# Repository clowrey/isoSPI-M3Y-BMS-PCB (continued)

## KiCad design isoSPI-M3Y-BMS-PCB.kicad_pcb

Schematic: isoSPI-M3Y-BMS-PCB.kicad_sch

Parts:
BT1, BT3, BT4, BT5, BT6, BT7, BT8, BT9: ~100V Brick
C1, C2, C55, C57: 10uF; C_0805_2012Metric; Voltage 50V; JLCPCB Part # C440198
C3, C4: 4.7uF 50V; C_1206_3216Metric; JLCPCB Part # C29823
C5, C94: 100nf; C_0603_1608Metric_Pad1.08x0.95mm_HandSolder; JLCPCB Part # C14663
C6, C24, C29: 10uF; C_0805_2012Metric; Voltage 50V X5R; JLCPCB Part # C440198
C7, C9, C49, C50, C51, C52, C62, C95, C132: 22uF; C_0805_2012Metric; Voltage 25V X5R; JLCPCB Part # C45783
C8: 10uF; C_0805_2012Metric_Pad1.18x1.45mm_HandSolder; Voltage 50V; JLCPCB Part # C440198
C10, C41, C42, C43: 100nf; C_0603_1608Metric; JLCPCB Part # C14663
C11, C38: 22uF; C_0805_2012Metric_Pad1.18x1.45mm_HandSolder; Voltage 25V; JLCPCB Part # C45783
C12, C13, C14, C15, C16, C21, C22, C23, C25, C28, C33, C44, C45, C54, C76, C79, C80, C81, C82, C85: 100nF; C_0603_1608Metric; JLCPCB Part # C14663
C17, C19, C20, C86: 1uF; C_0603_1608Metric; JLCPCB Part # v
C18: 1uF; C_0603_1608Metric; JLCPCB Part # C15849
C26, C40: 1uF; C_0603_1608Metric_Pad1.08x0.95mm_HandSolder; JLCPCB Part # C15849
C27, C32, C47, C61, C69, C72: 4.7u; C_0402_1005Metric; JLCPCB Part # C23733
C30, C31, C68: 100pF; C_0603_1608Metric; JLCPCB Part # C14858
C34, C112: 680uF; CP_Radial_D10.0mm_P5.00mm; Voltage 35V Polymer
C35, C36, C117, C118: 15pF; C_0402_1005Metric; JLCPCB Part # C1548
C37, C48, C87, C89: 4.7u; C_0402_1005Metric_small_pads; JLCPCB Part # C23733
C39, C56: 100nF; C_0603_1608Metric_Pad1.08x0.95mm_HandSolder; JLCPCB Part # C14663
C46, C58, C59, C60, C63, C64, C65, C66, C67, C70, C71, C73, C74, C75, C78, C120, C123, C124, C126, C127, C128, C129, C130, C131: 100n; C_0402_1005Metric; JLCPCB Part # C1525
C53: 4.7uF; C_0603_1608Metric; JLCPCB Part # C19666
D1, D7, D10, D25: SM15T36CA; D_SMC; JLCPCB Part # C1976312
D2, D3, D4, D8, D19, D38: Green; LED_0805_2012Metric; JLCPCB Part # C2297
D5, D23, D26, D29, D31, D32, D40: White; LED_0805_2012Metric; JLCPCB Part # C34499
D6, D9, D11, D14, D15, D21, D24, D30, D36, D39, D53: SS54; D_SMA; JLCPCB Part # C22452
D12, D13, D16, D17, D18, D20, D22, D27, D41, D42, D49, D50, D51: SMB6.8CA; D_SMB; JLCPCB Part # C78395
D28, D33, D34, D37: Red; LED_0805_2012Metric; JLCPCB Part # C84256
F1, F8: Pyro Fuse
F9, F11: 63A HV DC
FB1, FB7: 120Ω@100MHz; C_0603_1608Metric; JLCPCB Part # C14709
FB5: 600R@100MHz; L_0603_1608Metric_Pad1.05x0.95mm_HandSolder; JLCPCB Part # C1002
FL3: SDCW3225S-2-102TF; FILTER-SMD_4P-L3.2-W2.5-BL; JLCPCB Part # C192586
H1, H2, H3, H4, H5, H7, H12, H13: MountingHole_Pad; MountingHole_6.5mm
J1, J10: Screw_Terminal_01x04; PhoenixContact_MC_1,5_4-G-3.81_1x04_P3.81mm_Horizontal
J2, J13: Conn_02x10_Odd_Even; PinHeader_2x10_P2.54mm_Vertical
J3: 8P8C_LED_Shielded_x2; RJ45_Amphenol_RJHSE538X-02; JLCPCB Part # C3010546
J5: OEM Shunt Connector; CONN_ZE05H-8DP-2H_HIR
J6: 349128020; CONN_SD-34912-001_02_MOL; JLCPCB Part # C587318
J7: OEM HV Sense Connector; CONN_173864-1_TYC
J8: OEM Connector; S44BRAD1AK
J9, J16: Conn_01x03; PinHeader_1x03_P2.54mm_Vertical
J11: Screw_Terminal_01x03; PhoenixContact_MC_1,5_2-G-3.81_1x02_P3.81mm_Horizontal
J12: Screw_Terminal_01x08; PhoenixContact_MC_1,5_8-G-3.81_1x08_P3.81mm_Horizontal
J14: Screw_Terminal_01x04; PhoenixContact_GMSTBA_2,5_4-G-7,62_1x04_P7.62mm_Horizontal
J15, J17, J18: USB_C_Receptacle_USB2.0_16P; USB_C_Receptacle_HRO_TYPE-C-31-M-12
JP1, JP2, JP7, JP8: SolderJumper_3_Bridged12; SolderJumper-3_P1.3mm_Bridged12_RoundedPad1.0x1.5mm_NumberL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
JP3, JP4, JP5, JP6, JP13, JP14: SolderJumper_3_Open; SolderJumper-3_P1.3mm_Open_RoundedPad1.0x1.5mm_NumberLabels
JP9: SolderJumper_2_Bridged; SolderJumper-2_P1.3mm_Bridged_RoundedPad1.0x1.5mm
JP10, JP11, JP12: Jumper_2_Open; SolderJumper-2_P1.3mm_Open_RoundedPad1.0x1.5mm
K9, K14: Link Positive
K10, K16: FC Positive
K11, K17: FC Negative
K12, K15: Link Negative
K13, K18: Inverter
L1, L2, L4, L5: 6.8uh; L_Changjiang_FXL0630; JLCPCB Part # C167221
L3, L8: 22uh 5.5A; L_Changjiang_FXL1040; JLCPCB Part # C475917
L6, L7: 3.3u; L_pol_2016
Q1, Q2, Q3, Q5: CRSM034N06L2; AO_DFN-8-1EP_5.55x5.2mm_P1.27mm_EP4.12x4.6mm; JLCPCB Part # C467174
R1, R10: 150r; R_0603_1608Metric; JLCPCB Part # C22808
R2, R8: 2.2k; R_0603_1608Metric; JLCPCB Part # C4190
R3, R11, R27, R40, R41, R45, R47, R70, R74, R146: 24k; R_0603_1608Metric; JLCPCB Part # C23352
R4, R17, R25, R28, R62, R150: 100k; R_0603_1608Metric; JLCPCB Part # C25803
R5, R6, R26, R69, R90: 100R; R_0603_1608Metric; JLCPCB Part # C22775
R7, R9, R111, R112, R141: 510r; R_0603_1608Metric; JLCPCB Part # C23193
R12, R13, R14, R15, R20, R44, R53, R55, R82, R85, R174, R175: 5.1k; R_0603_1608Metric; JLCPCB Part # C23186
R16, R29, R48, R54, R56, R60, R66, R67, R68, R75, R77, R79, R83, R84, R140, R142, R143, R144, R148, R190: 10k; R_0603_1608Metric; JLCPCB Part # C25804
R18: 120r; R_1206_3216Metric; JLCPCB Part # C17909
R19, R33, R50, R58, R80, R171: 33r; R_0402_1005Metric; JLCPCB Part # C25105
R21, R24, R51, R52: 22R; R_0402_1005Metric; JLCPCB Part # C25092
R22, R31, R81: 10k; R_0603_1608Metric_Pad0.98x0.95mm_HandSolder; JLCPCB Part # C25804
R23, R36, R37, R38, R39, R42: 1.8k; R_0603_1608Metric; JLCPCB Part # C4177
R30: 100r; R_0603_1608Metric; JLCPCB Part # C22775
R32, R178: 25296nΩ
R34, R35, R43, R46, R49, R57, R59, R63, R64, R167, R168, R170: 1k; R_0402_1005Metric; JLCPCB Part # C11702
R61: 3k; R_0603_1608Metric; JLCPCB Part # C4211
R65: 2.7k; R_0603_1608Metric; JLCPCB Part # C13167
R94, R97: 1k; R_0603_1608Metric; JLCPCB Part # C21190
R98, R99, R100, R101, R102, R103, R104, R105, R106, R107, R108, R109, R110, R114, R115, R116, R126, R127, R130, R131, R134, R135, R153, R155, R193, R194, R195, R196, R214, R215, R216, R217, R218, R219, R220, R221, R222, R223, R224, R225, R226, R227: 1M; R_1206_3216Metric; JLCPCB Part # C17927
R149, R228, R229: 220r; R_0603_1608Metric; JLCPCB Part # C22962
R176: 27R 50W
SW1, SW2, SW3, SW4: TS-1187A-B-A-B; SW_Push_1P1T_XKB_TS-1187A; JLCPCB Part # C318884
TH1, TH2, TH3, TH4, TH5, TH6: B59451C1130B070; RV_Disc_D15.5mm_W7.5mm_P5.0mm; JLCPCB Part # C2762811
TP1, TP2, TP3, TP4, TP5, TP6, TP7, TP8, TP9, TP15, TP16, TP17, TP18, TP19: TestPoint_2Pole; TestPoint_2Pads_Pitch2.54mm_Pad1.5_Drill1.0mm
TP10, TP11, TP12, TP13, TP14: TP; TestPoint_THTPad_D1.5mm_Drill1.0mm
TR10: HM2113ZNLT; JLCPCB Part # C5730533
U1, U15, U23, U25, U26: SN74LV1T08DBVR; SOT-23-5; JLCPCB Part # C2682144
U2, U4, U30: ISO1540; SOIC-8_3.9x4.9mm_P1.27mm; JLCPCB Part # C179739
U3: INA228; VSSOP-10_3x3mm_P0.5mm; JLCPCB Part # C5214669
U6, U22, U24: F0505S-1WR3; Converter_DCDC_TRACO_TEA1-xxxxHI_THT; JLCPCB Part # C7465182
U8, U9, U10, U20: LTV-217-B-G; SSOP-4_4.4x2.6mm_P1.27mm; JLCPCB Part # C115450
U11, U27: RP2354B; RP2350-QFN-80-1EP_10x10_P0.4mm_EP3.4x3.4mm_ThermalVias; JLCPCB Part # C39843328
U12: ADS1115; TSSOP-10_3x3mm_P0.5mm; LCSC Part # C37593
U13: ISO1050DUB; SOP-8_6.62x9.15mm_P2.54mm; LCSC Part # C16428
U16: BatMan; LQFP-64_10x10mm_P0.5mm; JLCPCB Part # DNP
U17: TPS5430DDAR; TI_SO-PowerPAD-8_ThermalVias; LCSC Part C9864
U21: AMS1117-3.3; SOT-223-3_TabPin2; JLCPCB Part # C6186
U28: AM26LV32EIDR; SOIC-16_3.9x9.9mm_P1.27mm; JLCPCB Part # C527448
U29: B0505S-3WR2; Converter_DCDC_TRACO_TRA3-xxxx_THT; LCSC Part # C7500927
U32: SP3485EN-L/TR; SOIC-8_3.9x4.9mm_P1.27mm; JLCPCB Part # C8963
Y1, Y2: ABM8-272-T3; Crystal_SMD_3225-4Pin_3.2x2.5mm; JLCPCB Part # C20625731

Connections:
3.3V Sense: R66.2, R67.1, U27.49 (GPIO40_ADC0)
5V Sense: R140.1, R146.2, U27.52 (GPIO41_ADC1)
+1V1: C48.1, C71.1, C120.1, C123.1, L7.1, U27.10 (DVDD), U27.32 (DVDD), U27.51 (DVDD), U27.65 (VREG_FB)
+1V1_2: C46.1, C58.1, C70.1, C87.1, L6.1, U11.10 (DVDD), U11.32 (DVDD), U11.51 (DVDD), U11.65 (VREG_FB)
+3.3V: C13.1, C14.1, C37.1, C53.2, C59.1, C60.1, C63.1, C64.1, C65.1, C66.1, C67.1, C73.1, C74.1, C75.1, C78.1, C89.1, C124.1, C126.1, C127.1, C128.1, C129.1, C130.1, C131.1, J2.1, J2.3, J2.5, J2.7, J2.9, J13.1, J13.3, J13.5, J13.7, J13.9, R12.1, R13.1, R19.2, R33.2, R50.2, R58.2, R59.1, R65.2, R66.1, R75.1, R82.1, R85.1, R94.1, TP7.2, U2.1 (VCC1), U4.1 (VCC1), U8.4, U9.4, U11.5 (IOVDD), U11.15 (IOVDD), U11.24 (IOVDD), U11.29 (IOVDD), U11.41 (IOVDD), U11.50 (IOVDD), U11.60 (IOVDD), U11.64 (VREG_VIN), U11.68 (USB_OTP_VDD), U11.69 (QSPI_IOVDD), U11.76 (IOVDD), U13.1 (VCC1), U21.2 (VO), U27.5 (IOVDD), U27.15 (IOVDD), U27.24 (IOVDD), U27.29 (IOVDD), U27.41 (IOVDD), U27.50 (IOVDD), U27.60 (IOVDD), U27.64 (VREG_VIN), U27.68 (USB_OTP_VDD), U27.69 (QSPI_IOVDD), U27.76 (IOVDD), U30.1 (VCC1)
+3V3: C21.1, C22.2, C25.1, U1.5 (VCC), U28.4 (G), U28.16 (VDD), U32.8 (VCC)
+5V: C9.2, C11.2, C23.1, C49.2, C50.2, C52.2, C79.2, C80.2, C81.2, C82.2, C112.1, C132.2, FB1.2, FB7.2, L1.2, L2.2, L4.2, L5.2, L8.1, R60.1, R146.1, R190.1, TP8.2, U15.5 (VCC), U16.5 (5V), U16.41 (5V), U16.47 (5V), U21.3 (VI), U23.5 (VCC), U25.5 (VCC), U26.5 (VCC)
/CAN 5V: C6.2, C16.2, R23.2, R37.2, R77.1, R112.1, U13.8 (VCC2), U24.7 (+Vout)
/CAN H: C30.2, D16.2 (A2), FL3.2, JP1.3 (B), JP2.1 (A), JP3.3 (B), JP4.3 (B), JP5.3 (B), JP6.3 (B), JP13.3 (B), JP14.3 (B), R18.2, TP2.2
/CAN L: C31.1, D17.1 (A1), FL3.3, JP1.1 (A), JP2.3 (B), JP3.1 (A), JP4.1 (A), JP5.1 (A), JP6.1 (A), JP13.1 (A), JP14.1 (A), R18.1, TP2.1
/Contactor_Input: D15.2 (A), D20.2 (A2), D36.2 (A), J1.2
/FC Pos: K10.13, K16.13, K18.1, R176.2, TH1.2, TH2.2, TH3.2
/FC-Neg-Jumper: C44.2, D19.1 (K), D25.2 (A2), D39.2 (A), JP10.1 (A), JP11.1 (A), JP12.1 (A), Q3.5 (D)
/GPIO0: R57.2, U27.77 (GPIO0)
/GPIO3: J2.2, U27.80 (GPIO3)
/GPIO4: J2.4, U27.1 (GPIO4)
/GPIO5: J2.6, U27.2 (GPIO5)
/GPIO6: J2.8, U27.3 (GPIO6)
/GPIO7: J2.10, U27.4 (GPIO7)
/GPIO8: J2.12, U27.6 (GPIO8)
/GPIO9: J2.14, U27.7 (GPIO9)
/GPIO10: J2.16, U27.8 (GPIO10)
/GPIO11: J2.18, U27.9 (GPIO11)
/GPIO12: J2.20, U27.11 (GPIO12)
/GPIO25: R48.1, U27.26 (GPIO25)
/GPIO44_ADC4: U27.55 (GPIO44_ADC4)
/GPIO45_ADC5: U27.56 (GPIO45_ADC5)
/GPIO46_ADC6: U27.57 (GPIO46_ADC6)
/GPIO47_ADC7: U27.58 (GPIO47_ADC7)
/Grn: J3.6, JP14.2 (C)
/HV Sense 5V: C18.2, C39.2, C56.2, FB5.2, R20.1, R44.1, R54.1, R81.2, R228.1, U2.8 (VCC2), U12.8 (VDD)
/Logic_Input: D12.2 (A2), D14.2 (A), J1.4
/MCU2_GPIO0: R59.2, U11.77 (GPIO0)
/MCU2_GPIO1: R63.2, U11.78 (GPIO1)
/MCU2_GPIO2: R64.2, U11.79 (GPIO2)
/MCU2_GPIO3: U11.80 (GPIO3)
/MCU2_GPIO4: J13.2, U11.1 (GPIO4)
/MCU2_GPIO5: J13.4, U11.2 (GPIO5)
/MCU2_GPIO6: J13.6, U11.3 (GPIO6)
/MCU2_GPIO7: J13.8, U11.4 (GPIO7)
/MCU2_GPIO8: J13.10, U11.6 (GPIO8)
/MCU2_GPIO9: J13.12, U11.7 (GPIO9)
/MCU2_GPIO10: J13.14, U11.8 (GPIO10)
/MCU2_GPIO11: J13.16, U11.9 (GPIO11)
/MCU2_GPIO12: J13.18, U11.11 (GPIO12)
/MCU2_GPIO13: J13.20, U11.12 (GPIO13)
/MCU2_GPIO15: U11.14 (GPIO15)
/MCU2_GPIO16: U11.16 (GPIO16)
/MCU2_GPIO17: U11.17 (GPIO17)
/MCU2_GPIO18: U11.18 (GPIO18)
/MCU2_GPIO19: U11.19 (GPIO19)
/MCU2_GPIO20: U11.20 (GPIO20)
/MCU2_GPIO21: U11.21 (GPIO21)
/MCU2_GPIO22: U11.22 (GPIO22)
/MCU2_GPIO23: U11.23 (GPIO23)
/MCU2_GPIO24: U11.25 (GPIO24)
/MCU2_GPIO25: R56.1, U11.26 (GPIO25)
/MCU2_GPIO26: U11.27 (GPIO26)
/MCU2_GPIO27: U11.28 (GPIO27)
/MCU2_GPIO33: U11.42 (GPIO33)
/MCU2_GPIO34: U11.43 (GPIO34)
/MCU2_GPIO35: U11.44 (GPIO35)
/MCU2_GPIO36: U11.45 (GPIO36)
/MCU2_GPIO37: U11.46 (GPIO37)
/MCU2_GPIO38: R34.2, U11.47 (GPIO38)
/MCU2_GPIO39: R35.2, U11.48 (GPIO39)
/PH: C54.1, D24.1 (K), L8.2, U17.8 (PH)
/QSPI2_SCLK: U11.71 (QSPI_SCLK)
/QSPI2_SD0: U11.72 (QSPI_SD0)
/QSPI2_SD1: U11.74 (QSPI_SD1)
/QSPI2_SD2: U11.73 (QSPI_SD2)
/QSPI2_SD3: U11.70 (QSPI_SD3)
/QSPI2_SS: R49.1, U11.75 (QSPI_SS)
/QSPI_SCLK: U27.71 (QSPI_SCLK)
/QSPI_SD0: U27.72 (QSPI_SD0)
/QSPI_SD1: U27.74 (QSPI_SD1)
/QSPI_SD2: U27.73 (QSPI_SD2)
/QSPI_SD3: U27.70 (QSPI_SD3)
/QSPI_SS: R170.1, U27.75 (QSPI_SS)
/RUN: R167.2, SW4.2
/RUN_2: R43.1, U11.35 (RUN)
/SWCLK: J16.1, U27.33 (SWCLK)
/SWCLK_2: J9.1, U11.33 (SWCLK)
/SWD: J16.3, U27.34 (SWD)
/SWD_2: J9.3, U11.34 (SWD)
/Serial API 5V: C12.2, C24.2, D21.2 (A), R97.1, R141.1, R142.1, U29.6 (+Vout), U30.8 (VCC2)
/Serial API RX: D42.1 (A1), J15.A7 (D-), J15.B7 (D-), R143.1, TP19.1, U30.6 (SCL2)
/Serial API TX: D41.2 (A2), J15.A6 (D+), J15.B6 (D+), R97.2, TP19.2, U30.7 (SDA2)
/USB2_D+: J17.A6 (D+), J17.B6 (D+), R51.1
/USB2_D-: J17.A7 (D-), J17.B7 (D-), R52.1
/USB_D+: J18.A6 (D+), J18.B6 (D+), R21.1
/USB_D-: J18.A7 (D-), J18.B7 (D-), R24.1
/VREG2_AVDD: C32.1, R33.1, U11.61 (VREG_AVDD)
/VREG2_LX: L6.2, U11.63 (VREG_LX)
/VREG_AVDD: C61.1, R19.1, U27.61 (VREG_AVDD)
/VREG_LX: L7.2, U27.63 (VREG_LX)
/V_cont1: C2.2, D15.1 (K), D36.1 (K), L3.2
/Wht-Grn: J3.3, JP13.2 (C)
/XIN: C117.1, U27.30 (XIN), Y2.1
/XIN_2: C35.1, U11.30 (XIN), Y1.1
/XOUT: R168.1, U27.31 (XOUT)
/XOUT_2: R46.1, U11.31 (XOUT)
/iso+: C68.2, JP7.2 (C), R90.1, TP18.1, TR10.1 (TD-)
/iso-: C68.1, JP8.2 (C), R90.2, TP18.2, TR10.3 (TD+)
BatSPI_EN: U16.42 (EN), U27.46 (GPIO37)
BatSPI_SCK: U16.56 (SPI_SCK), U27.43 (GPIO34)
Batman IsoSPI+: JP8.3 (B), U16.62 (A-BMB)
Batman IsoSPI-: JP7.3 (B), U16.61 (A-BMB)
Batt Negative: J7.10, J14.4, R225.2
Batt Positive: J7.1, J14.1, R224.2
C FC-Neg (GND): J8.37, J12.2, JP10.2 (B), JP11.2 (B), JP12.2 (B)
C FC-Pos (GND): C33.2, D1.2 (A2), D4.1 (K), D11.2 (A), J8.36, J12.4, Q2.5 (D)
C Neg (GND): C15.2, D3.1 (K), D6.2 (A), D7.2 (A2), J8.42, J12.6, Q1.5 (D)
C Pos (GND): C45.2, D8.1 (K), D9.2 (A), D10.2 (A2), J8.41, J12.8, Q5.5 (D)
CAN Rx: R83.1, TP6.1, U13.2 (RXD), U27.19 (GPIO19)
CAN Tx: R84.1, TP6.2, U13.3 (TXD), U27.20 (GPIO20)
C_En: U11.13 (GPIO14), U15.2, U23.2, U25.2, U26.2
Drive Unit Pos: F9.1, K9.13, K10.14, K14.13, K16.14, TH4.1, TH5.1, TH6.1
Emergency Stop: R22.2, U8.3
Extra Input: R31.2, U9.3
Extra Output 1: R39.2, U27.12 (GPIO13)
Extra Output 2: R38.2, U27.13 (GPIO14)
FC Negative: J7.7, J14.3, R227.2
FC Positive: J7.4, J14.2, R226.2
FC-Neg: U26.1, U27.14 (GPIO15)
FC-Pos: U25.1, U27.18 (GPIO18)
GND: C1.1, C2.1, C7.1, C9.1, C11.1, C13.2, C14.2, C15.1, C21.2, C22.1, C23.2, C25.2, C27.2, C32.2, C33.1, C34.2, C35.2, C36.2, C37.2, C38.1, C44.1, C45.1, C46.2, C47.2, C48.2, C49.1, C50.1, C51.1, C52.1, C53.1, C55.1, C57.1, C58.2, C59.2, C60.2, C61.2, C62.1, C63.2, C64.2, C65.2, C66.2, C67.2, C69.2, C70.2, C71.2, C72.2, C73.2, C74.2, C75.2, C78.2, C79.1, C80.1, C81.1, C82.1, C85.1, C87.2, C89.2, C112.2, C117.2, C118.2, C120.2, C123.2, C124.2, C126.2, C127.2, C128.2, C129.2, C130.2, C131.2, C132.1, D1.1 (A1), D2.1 (K), D5.1 (K), D7.1 (A1), D10.1 (A1), D22.1 (A1), D23.1 (K), D24.2 (A), D25.1 (A1), D26.1 (K), D28.1 (K), D33.1 (K), D34.1 (K), D37.1 (K), D49.1 (A1), D51.1 (A1), J1.1, J1.3, J2.11, J2.13, J2.15, J2.17, J2.19, J9.2, J13.11, J13.13, J13.15, J13.17, J13.19, J16.2, J17.A1 (GND), J17.A12 (GND), J17.B1 (GND), J17.B12 (GND), J17.S1 (SHIELD), J18.A1 (GND), J18.A12 (GND), J18.B1 (GND), J18.B12 (GND), J18.S1 (SHIELD), Q1.1 (S), Q1.2 (S), Q1.3 (S), Q2.1 (S), Q2.2 (S), Q2.3 (S), Q3.1 (S), Q3.2 (S), Q3.3 (S), Q5.1 (S), Q5.2 (S), Q5.3 (S), R4.1, R17.1, R22.1, R25.1, R29.2, R31.1, R53.1, R55.1, R57.1, R62.1, R67.2, R99.1, R140.2, R148.2, R149.2, R174.1, R175.1, SW1.1, SW2.1, SW3.1, SW4.1, TP7.1, TP8.1, TP15.1, TP16.1, U1.3 (GND), U2.4 (GND1), U4.4 (GND1), U6.2 (-Vin), U10.2, U11.62 (VREG_PGND), U11.81 (GND), U13.4 (GND1), U15.3 (GND), U16.1 (GND), U16.3 (GND), U16.6 (GND), U16.7 (GND), U16.8 (GND), U16.9 (GND), U16.10 (GND), U16.11 (GND), U16.12 (GND), U16.13 (GND), U16.14 (GND), U16.15 (GND), U16.16 (GND), U16.17 (GND), U16.18 (GND), U16.19 (GND), U16.20 (GND), U16.21 (GND), U16.22 (GND), U16.23 (GND), U16.24 (GND), U16.25 (GND), U16.26 (GND), U16.27 (GND), U16.28 (GND), U16.29 (GND), U16.30 (GND), U16.31 (GND), U16.33 (GND), U16.34 (GND), U16.35 (GND), U16.36 (GND), U16.37 (GND), U16.38 (GND), U16.39 (GND), U16.40 (GND), U16.43 (GND), U16.45 (GND), U16.46 (GND), U16.49 (GND), U16.51 (GND), U16.60 (GND), U17.6 (GND), U17.9 (PowerPAD), U20.2, U21.1 (GND), U22.2 (-Vin), U23.3 (GND), U24.2 (-Vin), U25.3 (GND), U26.3 (GND), U27.62 (VREG_PGND), U27.81 (GND), U28.8 (GND), U28.12 (~G), U29.2 (-Vin), U30.4 (GND1), U32.2 (~RE), U32.5 (GND), Y1.2, Y1.4, Y2.2, Y2.4
GND CAN: C6.1, C16.1, C30.1, C31.2, D16.1 (A1), D17.2 (A2), D29.1 (K), J3.19, J3.SH, R112.2, U13.5 (GND2), U24.5 (-Vout)
GND Shunt NTC -: C3.1, C4.2, C28.1, C29.1, C76.1, C94.1, D31.1 (K), J5.1, J5.3, J10.2, R7.1, R9.2, R111.2, U3.1 (A1), U3.2 (A0), U3.7 (GND), U4.5 (GND2), U22.5 (-Vout)
GND_RS: C12.1, C24.1, D38.1 (K), D40.1 (K), D41.1 (A1), D42.2 (A2), J15.A1 (GND), J15.A12 (GND), J15.B1 (GND), J15.B12 (GND), J15.S1 (SHIELD), R141.2, U29.4 (-Vout), U30.5 (GND2)
GND_VSens: C8.1, C18.1, C39.1, C56.1, C95.1, D32.1 (K), R229.2, TP12.1, U2.5 (GND2), U6.5 (-Vout), U12.1 (ADDR), U12.3 (GND)
HMI Serial RX: R35.1, R94.2, TP5.2, U27.48 (GPIO39), U30.3 (SCL1)
HMI Serial TX: R34.1, R144.1, TP5.1, U27.47 (GPIO38), U30.2 (SDA1)
I2C SCL Shunt: R12.2, TP3.2, U4.3 (SCL1), U27.23 (GPIO23)
I2C SCL Vsense: R82.2, TP4.2, U2.3 (SCL1), U27.21 (GPIO21)
I2C SDA Shunt: R13.2, TP3.1, U4.2 (SDA1), U27.25 (GPIO24)
I2C SDA Vsense: R85.2, TP4.1, U2.2 (SDA1), U27.22 (GPIO22)
IsoSPI RX AND: U1.4, U11.38 (GPIO30), U27.38 (GPIO30)
IsoSPI RX Debug: TP16.2, U11.39 (GPIO31), U27.39 (GPIO31)
IsoSPI RX H: TP17.1, U1.2, U11.36 (GPIO28), U27.36 (GPIO28), U28.5 (2Y)
IsoSPI RX L: TP17.2, U1.1, U11.37 (GPIO29), U27.37 (GPIO29), U28.3 (1Y)
IsoSPI TX Data: TP1.2, U27.28 (GPIO27), U32.4 (DI)
IsoSPI TX En: TP1.1, U27.27 (GPIO26), U32.3 (DE)
IsoSPI+: J6.1, J11.1, TR10.4 (TX+)
IsoSPI-: J6.2, J11.2, TR10.6 (TX-)
Link Negative: J7.22
Link Positive: J7.13
MAIN-SUP TX/RX: R64.1, TP9.2, U27.78 (GPIO1)
Neg: U23.1, U27.16 (GPIO16)
unnamed: BT1.1 (+), BT5.2 (-)
unnamed: BT1.2 (-), R32.2
unnamed: BT3.1 (+), F8.1
unnamed: BT3.2 (-), BT4.1 (+)
unnamed: BT4.2 (-), BT9.2 (-), K12.14, K15.14
unnamed: BT5.1 (+), BT6.1 (+), K9.14, K14.14, R176.1
unnamed: BT6.2 (-), BT7.1 (+)
unnamed: BT7.2 (-), R178.1
unnamed: BT8.1 (+), F1.1
unnamed: BT8.2 (-), BT9.1 (+)
unnamed: C3.2, R8.2, R10.1
unnamed: C4.1, R1.1, R2.2
unnamed: C10.1, C41.2, C42.1, C43.2, C95.2, R40.2, R41.1, R45.2, R47.1, R228.2, R229.1
unnamed: C26.1, J3.14, J3.23, U9.2
unnamed: C26.2, R36.1, U9.1
unnamed: C27.1, R50.1, R80.2
unnamed: C36.1, R46.2, Y1.3
unnamed: C40.1, J3.20, J3.21, U8.2
unnamed: C40.2, R23.1, U8.1
unnamed: C69.1, R58.1, R171.2
unnamed: C118.1, R168.2, Y2.3
unnamed: D2.2 (A), R83.2
unnamed: D3.2 (A), R11.2
unnamed: D4.2 (A), R27.2
unnamed: D5.2 (A), R74.2
unnamed: D8.2 (A), R3.2
unnamed: D12.1 (A1), D13.2 (A2)
unnamed: D13.1 (A1), D22.2 (A2)
unnamed: D18.1 (A1), D50.2 (A2)
unnamed: D19.2 (A), R70.2
unnamed: D20.1 (A1), D27.2 (A2)
unnamed: D21.1 (K), J15.A4 (VBUS), J15.A9 (VBUS), J15.B4 (VBUS), J15.B9 (VBUS)
unnamed: D23.2 (A), R190.2
unnamed: D26.2 (A), R75.2
unnamed: D27.1 (A1), D49.2 (A2)
unnamed: D28.2 (A), R84.2
unnamed: D29.2 (A), R77.2
unnamed: D30.2 (A), J17.A4 (VBUS), J17.A9 (VBUS), J17.B4 (VBUS), J17.B9 (VBUS)
unnamed: D30.1 (K), FB1.1
unnamed: D31.2 (A), R79.2
unnamed: D32.2 (A), R81.1
unnamed: D33.2 (A), R48.2
unnamed: D34.2 (A), R56.2
unnamed: D37.2 (A), R144.2
unnamed: D38.2 (A), R143.2
unnamed: D40.2 (A), R142.2
unnamed: D50.1 (A1), D51.2 (A2)
unnamed: D53.2 (A), J18.A4 (VBUS), J18.A9 (VBUS), J18.B4 (VBUS), J18.B9 (VBUS)
unnamed: D53.1 (K), FB7.1
unnamed: F1.2, R178.4
unnamed: F8.2, R32.1
unnamed: F9.2, K13.1
unnamed: F11.1, K11.14, K12.13, K13.2, K15.13, K17.14
unnamed: F11.2, K11.13, K17.13, K18.2
unnamed: J3.13, R36.2, R42.2
unnamed: J3.15, U20.4
unnamed: J3.16, U10.3
unnamed: J3.17, U10.4
unnamed: J3.18, U20.3
unnamed: J3.22, R37.1
unnamed: J3.24, R42.1
unnamed: J17.A5 (CC1), R53.2
unnamed: J17.B5 (CC2), R55.2
unnamed: J18.A5 (CC1), R174.2
unnamed: J18.B5 (CC2), R175.2
unnamed: J3.5, JP1.2 (C)
unnamed: J3.4, JP2.2 (C)
unnamed: J3.8, JP3.2 (C)
unnamed: J3.7, JP4.2 (C)
unnamed: J3.2, JP5.2 (C)
unnamed: J3.1, JP6.2 (C)
unnamed: C20.1, C86.1, JP7.1 (A), U32.6 (A)
unnamed: C17.1, C19.1, JP8.1 (A), U32.7 (B)
unnamed: JP9.1 (A), TR10.2 (C_TD)
unnamed: C85.2, JP9.2 (B)
unnamed: Q1.4 (G), R5.2
unnamed: Q2.4 (G), R6.2
unnamed: Q3.4 (G), R69.2
unnamed: Q5.4 (G), R26.2
unnamed: R4.2, R5.1, U23.4
unnamed: R6.1, R17.2, U25.4
unnamed: R25.2, R26.1, U15.4
unnamed: R30.1, U16.64 (B-BMB)
unnamed: R30.2, U16.63 (B-BMB)
unnamed: R38.1, U20.1
unnamed: R39.1, U10.1
unnamed: R43.2, SW2.2
unnamed: R49.2, SW1.2
unnamed: R62.2, R69.1, U26.4
unnamed: R98.1, R99.2
unnamed: R100.2, R104.1
unnamed: R101.2, R105.1
unnamed: R102.2, R106.1
unnamed: R103.2, R107.1
unnamed: R104.2, R108.1
unnamed: R105.2, R109.1
unnamed: R106.2, R110.1
unnamed: R107.2, R114.1
unnamed: R108.2, R115.1
unnamed: R109.2, R116.1
unnamed: R110.2, R126.1
unnamed: R114.2, R127.1
unnamed: R115.2, R130.1
unnamed: R116.2, R131.1
unnamed: R126.2, R134.1
unnamed: R127.2, R135.1
unnamed: R130.2, R153.1
unnamed: R131.2, R155.1
unnamed: R134.2, R193.1
unnamed: R135.2, R194.1
unnamed: R61.2, R149.1
unnamed: R153.2, R195.1
unnamed: R155.2, R196.1
unnamed: R170.2, SW3.2
unnamed: R193.2, R214.1
unnamed: R194.2, R215.1
unnamed: R195.2, R216.1
unnamed: R196.2, R217.1
unnamed: R214.2, R218.1
unnamed: R215.2, R219.1
unnamed: R216.2, R220.1
unnamed: R217.2, R221.1
unnamed: R218.2, R222.1
unnamed: R219.2, R223.1
unnamed: R220.2, R224.1
unnamed: R221.2, R225.1
unnamed: R222.2, R226.1
unnamed: R223.2, R227.1
unnamed: TH1.1, TH2.1, TH3.1, TH4.2, TH5.2, TH6.2
unnamed: R98.2, TR10.5 (C_TX)
unnamed: R15.2, U3.5 (SCL), U4.6 (SCL2)
unnamed: R14.2, U3.4 (SDA), U4.7 (SDA2)
unnamed: C5.2, R2.1, U3.10 (Vin+)
unnamed: C5.1, R8.1, U3.9 (Vin-)
unnamed: R68.2, U3.3 (~Alert)
unnamed: C38.2, L2.1, U6.1 (+Vin)
unnamed: C8.2, FB5.1, U6.7 (+Vout)
unnamed: C47.1, R80.1, U11.59 (ADC_AVDD)
unnamed: R52.2, U11.66 (USB_DM)
unnamed: R51.2, U11.67 (USB_DP)
unnamed: C10.2, R40.1, R100.1, TP14.1, U12.4 (AIN0)
unnamed: C41.1, R41.2, R101.1, TP13.1, U12.5 (AIN1)
unnamed: C42.2, R45.1, R102.1, TP11.1, U12.6 (AIN2)
unnamed: C43.1, R47.2, R103.1, TP10.1, U12.7 (AIN3)
unnamed: R54.2, U12.2 (ALERT/RDY)
unnamed: R44.2, U2.6 (SCL2), U12.10 (SCL)
unnamed: R20.2, U2.7 (SDA2), U12.9 (SDA)
unnamed: FL3.1, U13.7 (CANH)
unnamed: FL3.4, U13.6 (CANL)
unnamed: C54.2, U17.1 (BOOT)
unnamed: R60.2, R61.1, U17.4 (VSENSE)
unnamed: C7.2, L1.1, U22.1 (+Vin)
unnamed: C62.2, L5.1, U24.1 (+Vin)
unnamed: C72.1, R171.1, U27.59 (ADC_AVDD)
unnamed: R167.1, U27.35 (RUN)
unnamed: R24.2, U27.66 (USB_DM)
unnamed: R21.2, U27.67 (USB_DP)
unnamed: C86.2, U28.2 (1A)
unnamed: C17.2, U28.1 (1B)
unnamed: C19.2, U28.6 (2A)
unnamed: C20.2, U28.7 (2B)
unnamed: C51.2, L4.1, U29.1 (+Vin)
Pos: U15.1, U27.17 (GPIO17)
SUP-MAIN TX/RX: R63.1, TP9.1, U27.79 (GPIO2)
Shunt Midpoint: J5.8
Shunt NTC +: C94.2, J5.7, J10.1, R16.1, U3.8 (Vbus)
Shunt Passive +: J5.6
Shunt Sense +: J5.5, J10.3, R1.2, R7.2
Shunt Sense -: J5.4, J10.4, R9.1, R10.2
Shunt_5V: C28.2, C29.2, C76.2, R14.1, R15.1, R16.2, R68.1, R79.1, R111.1, U3.6 (VS), U4.8 (VCC2), U22.7 (+Vout)
Snooper Debug: TP15.2, U11.40 (GPIO32), U27.40 (GPIO32)
VContactor Sense: R28.1, R29.1, U27.54 (GPIO43_ADC3)
V_{Contactor}: C1.2, C34.1, D6.1 (K), D9.1 (K), D11.1 (K), D18.2 (A2), D39.1 (K), J8.33, J8.34, J8.35, J8.43, J12.1, J12.3, J12.5, J12.7, L3.1, R3.1, R11.1, R27.1, R28.2, R70.1
V_{in}: C55.2, C57.2, D14.1 (K), R74.1, R150.2, U17.7 (VIN)
Vin Logic Sense: R148.1, R150.1, U27.53 (GPIO42_ADC2)

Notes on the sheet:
all JLC basic components
3.3V 1A LDO Supply
GPIO3 - GPIO12 on NC header
FC Negative Contactor
Would be cool if it alternates with main
PTC 440V 56Ω
BMB side xfmr center tap has no connection reference to ground to prevent ESD
unused inputs left floating - internal bias
3A max output - 3.3V draws from this rail
Galvanically Isolated Area
100k input impedance 0.14mA typical ADC usage
Terminate unused port per LTC6813 datasheet (100R recommended)
MCU Identification
In tesla packs the shunt is at the mid point of the pack!
Supervisor MCU
5V powers exteral ESP32 LCD also
FC Positive Contactor
Cells Positive Contactor
close to MCU
Extra GPIO
API TTL RS232 Interface
Redundant connectors
isoSPI Transceiver
Shunt Current Sense
Cells Positive Always Live
10V-16V input
Data must be after En
Positives
all JLC basic components except: inductor, 680uf cap
1A max output
Inverter connected to FC port
5V 3A DC-DC Supply
5V 600mA max external ESP32 interface
BatMan Interface
Inverter CAN Interface
Cells Negative Contactor
I2C ADDR: 0x48
requires connection to always live terminal
Contactor AND gate enable output
Main MCU

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
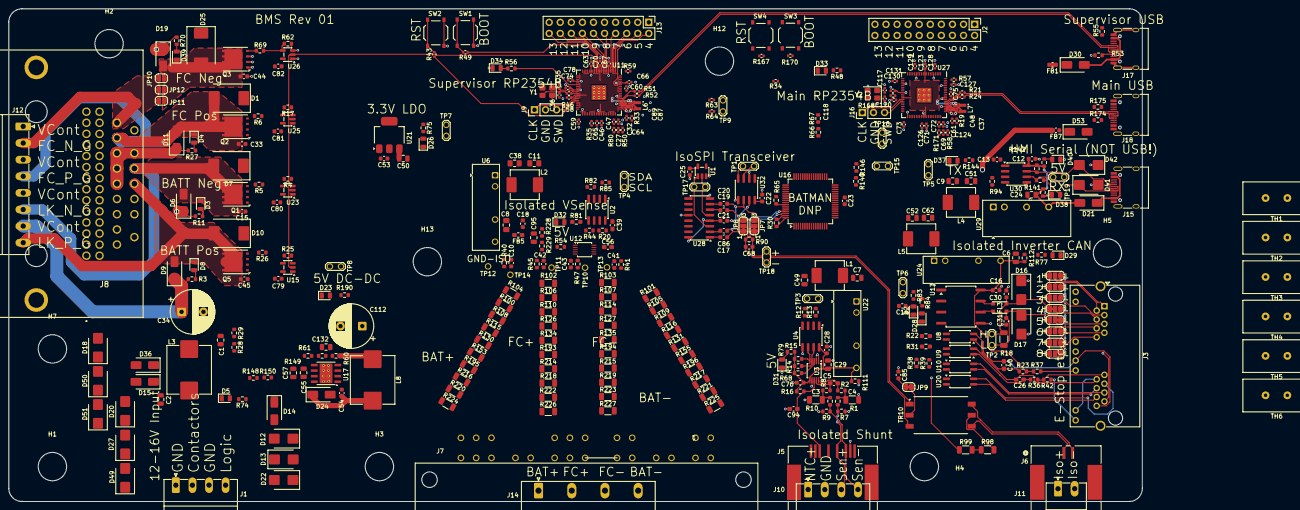
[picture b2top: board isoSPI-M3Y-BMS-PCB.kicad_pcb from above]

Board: 4 copper layers, 260.0 x 113.0 mm, 402 parts (0 on the bottom side), 275 nets.

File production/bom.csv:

Designator,Footprint,Quantity,Value,LCSC Part #
"C1, C2, C24, C29, C55, C57, C6, C8",0805,8,10uF,C440198
"C10, C12, C13, C14, C15, C16, C21, C22, C23, C25, C28, C33, C39, C41, C42, C43, C44, C45, C5, C54, C56, C76, C77, C79, C80, C81, C82, C83, C84, C85, C88, C94",0603,32,100nf,C14663
"C11, C132, C38, C49, C50, C51, C52, C62, C7, C9, C95",0805,11,22uF,C45783
"C112, C34, C69",CP_Radial_D10.0mm_P5.00mm,3,680uF,C46550429
"C117, C118, C35, C36",0402,4,15pF,C1548
"C120, C123, C124, C126, C127, C128, C129, C130, C131, C46, C58, C59, C60, C63, C64, C65, C66, C67, C70, C71, C73, C74, C75, C78",0402,24,100n,C1525
"C17, C19, C20, C86",0603,4,1uF,v
"C18, C26, C27, C40, C90",0603,5,1uF,C15849
"C3, C4",1206,2,4.7uF 50V,C29823
"C30, C31, C68",0603,3,100pF,C14858
"C32, C37, C47, C48, C61, C72, C87, C89",0402,8,4.7u,C23733
C53,0603,1,4.7uF,C19666
"D1, D10, D25, D7",D_SMC,4,SMCJ33CA,C224050
"D11, D14, D15, D21, D24, D30, D36, D39, D53, D6, D9",D_SMA,11,SS54,C22452
"D12, D13, D16, D17, D18, D20, D22, D27, D41, D42, D49, D50, D51",D_SMB,13,SMB6.8CA,C78395
"D19, D2, D3, D38, D4, D8",0805,6,Green,C2297
"D23, D26, D29, D31, D32, D35, D40, D5",0805,8,White,C34499
"D28, D33, D34, D37",0805,4,Red,C84256
"FB1, FB7",0603,2,120Ω@100MHz,C14709
FB5,0603,1,600R@100MHz,C1002
FL3,FILTER-SMD_4P-L3.2-W2.5-BL,1,SDCW3225S-2-102TF,C192586
"J15, J17, J18",USB_C_Receptacle_HRO_TYPE-C-31-M-12,3,USB_C_Receptacle_USB2.0_16P,C2765186
"J16, J9",PinHeader_1x03_P2.54mm_Vertical,2,Conn_01x03,
J3,RJ45_Amphenol_RJHSE538X-02,1,8P8C_LED_Shielded_x2,C3010546
J6,CONN_SD-34912-001_02_MOL,1,OEM Connector,C587318
"JP10, JP11, JP12",SolderJumper-2_P1.3mm_Open_RoundedPad1.0x1.5mm,3,Jumper_2_Open,
"L1, L2, L4, L5",L_Changjiang_FXL0630,4,6.8uh,C167221
"L3, L8",L_Changjiang_FXL1040,2,22uh 5.5A,C475917
"L6, L7",L_pol_2016,2,3.3uh,C42411119
"Q1, Q2, Q3, Q5",AO_DFN-8-1EP_5.55x5.2mm_P1.27mm_EP4.12x4.6mm,4,CRSM034N06L2,C467174
"R1, R10",0603,2,150r,C22808
"R100, R101, R102, R103, R104, R105, R106, R107, R108, R109, R110, R114, R115, R116, R126, R127, R130, R131, R134, R135, R153, R155, R193, R194, R195, R196, R214, R215, R216, R217, R218, R219, R220, R221, R222, R223, R224, R225, R226, R227, R98, R99",1206,42,1M,C17927
"R11, R146, R27, R3, R40, R41, R45, R47, R70, R74, R76",0603,11,24k,C23352
"R111, R112, R61, R7, R9",0603,5,510r,C23193
"R12, R13, R14, R15, R174, R175, R20, R44, R53, R55, R82, R85",0603,12,5.1k,C23186
"R140, R142, R143, R144, R148, R16, R190, R22, R29, R31, R48, R50, R54, R56, R66, R67, R68, R73, R75, R77, R79, R81, R83, R84",0603,24,10k,C25804
"R149, R167, R168, R170, R34, R35, R43, R46, R49, R57, R59, R63, R64",0402,13,1k,C11702
"R150, R17, R25, R28, R4, R62",0603,6,100k,C25803
"R171, R19, R33, R80",0402,4,33r,C25105
R18,1206,1,120r,C17909
"R2, R37, R39, R8",0603,4,2.2k,C4190
"R21, R24, R51, R52",0402,4,22R,C25092
"R228, R229",0603,2,220r,C22962
"R23, R36, R38, R58, R71, R72, R78, R94, R97",0603,9,1k,C21190
"R26, R30, R5, R6, R69, R90",0603,6,100R,C22775
R60,0402,1,3.3k,C25890
R65,0603,1,2.7k,C13167
"SW1, SW2, SW3, SW4",SW_Push_1P1T_XKB_TS-1187A,4,TS-1187A-B-A-B,C318884
"TH1, TH2, TH3, TH4, TH5, TH6",RV_Disc_D15.5mm_W7.5mm_P5.0mm,6,B59451C1130B070,C2762811
"TP1, TP15, TP16, TP17, TP18, TP19, TP2, TP20, TP21, TP3, TP4, TP5, TP6, TP7, TP8, TP9",TestPoint_2Pads_Pitch2.54mm_Pad1.5_Drill1.0mm,16,TestPoint_2Pole,
"TP10, TP11, TP12, TP13, TP14, TP22, TP23, TP24, TP25, TP26, TP27, TP28, TP29, TP30, TP31, TP32, TP33, TP34, TP35, TP36, TP37, TP38",TestPoint_THTPad_D1.5mm_Drill1.0mm,22,TP,
TR10,HM2113ZNLT,1,HM2113ZNLT,C5730533
"U1, U15, U23, U25, U26",SOT-23-5,5,SN74LV1T08DBVR,C2682144
"U10, U20, U5, U7, U8, U9",SSOP-4_4.4x2.6mm_P1.27mm,6,LTV-217-B-G,C115450
"U11, U27",RP2350-QFN-80-1EP_10x10_P0.4mm_EP3.4x3.4mm_ThermalVias,2,RP2354B,C39843328
U12,TSSOP-10_3x3mm_P0.5mm,1,ADS1115,C37593
U13,SOP-8_6.62x9.15mm_P2.54mm,1,ISO1050DUB,C16428
U17,TI_SO-PowerPAD-8_ThermalVias,1,TPS5430DDAR,C9864
"U2, U30, U4",SOIC-8_3.9x4.9mm_P1.27mm,3,ISO1540,C179739
U21,SOT-223-3_TabPin2,1,AMS1117-3.3,C6186
"U22, U24, U6",H0505S-1WR2,3,F0505S-1WR3,C7465182
U28,SOIC-16_3.9x9.9mm_P1.27mm,1,AM26LV32EIDR,C527448
U29,Converter_DCDC_TRACO_TRA3-xxxx_THT,1,B0505S-3WR2,C7500927
U3,VSSOP-10_3x3mm_P0.5mm,1,INA228,C5214669
U32,SOIC-8_3.9x4.9mm_P1.27mm,1,SP3485EN-L/TR,C8963
"Y1, Y2",Crystal_SMD_3225-4Pin_3.2x2.5mm,2,ABM8-272-T3,C20625731

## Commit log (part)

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2025-12-03 update gitignore
2025-12-03 cleanup the pcb more
2025-12-03 more updates
2025-12-03 connect remaining gpio
2025-12-03 rename serial
2025-12-04 progress...
2025-12-05 more routing
2025-12-05 getting close!
2025-12-05 progress
2025-12-05 fix more drc violations
2025-12-05 fix unconnected
2025-12-06 lots more
